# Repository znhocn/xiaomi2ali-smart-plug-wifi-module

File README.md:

# Xiaomi2Ali Smart Plug WiFi Module

Xiaomi Smart Plug WiFi Module to Ali 86 Smart Plug Adapter board

此项目是把从[米家智能插座基础版](https://www.mi.com/mj-socket/)里拆卸下来的 WiFi 模块转换成可供阿里智能插座-86型墙壁插座使用的模块。

使用小米的 WiFi 模块替换原有阿里智能的 WiFi 模块，实现使用米家APP控制插座，并且支持小爱同学控制。

目前米家生态链里没有直接使用 WiFi 的86型墙壁智能插座。

支持阿里86型墙壁插座的 10A 与 16A 的 WiFi 模块兼容性。

发给 PCB 厂家生产时建议使用 [Rev.B](Gerber/Rev.B) 版本。

某些厂家可能不支持半孔覆铜工艺，可用 Rev.B 版本发给厂家去生产。

使用 Rev.B 生产的 PCB 需要自己在通孔焊盘上划一刀再掰开，有必要还可以用锉刀再打磨一下断裂处。

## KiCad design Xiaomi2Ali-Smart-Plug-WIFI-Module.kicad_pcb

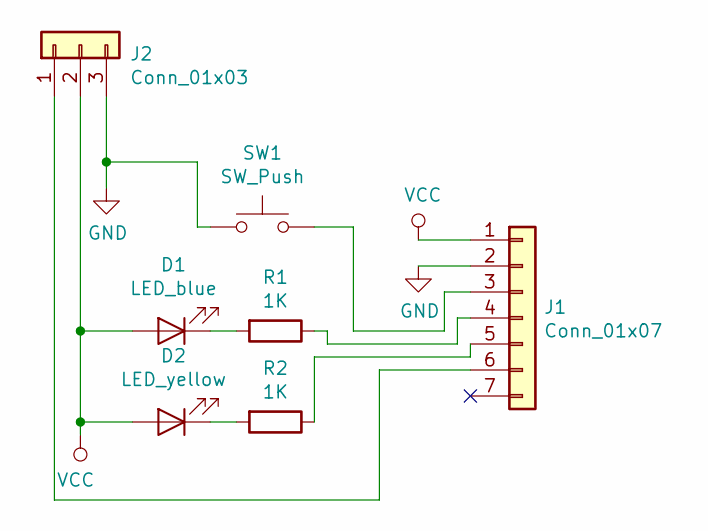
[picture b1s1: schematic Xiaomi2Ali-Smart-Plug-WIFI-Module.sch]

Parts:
D1: LED_blue; LED_1206_3216Metric
D2: LED_yellow; LED_1206_3216Metric
J1: Conn_01x07; PinHeader_1x07_P2.00mm_Vertical
J2: Conn_01x03; PinHeader_1x03_P2.54mm_Vertical
R1, R2: 1K; R_1206_3216Metric
SW1: SW_Push; SW_SPST_B3S-1000

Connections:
GND: J1.2, J2.3, SW1.1
unnamed: D1.1 (K), R1.2
unnamed: D2.1 (K), R2.2
unnamed: J1.3, SW1.2
unnamed: J1.4, R1.1
unnamed: J1.5, R2.1
unnamed: J1.6, J2.1
VCC: D1.2 (A), D2.2 (A), J1.1, J2.2

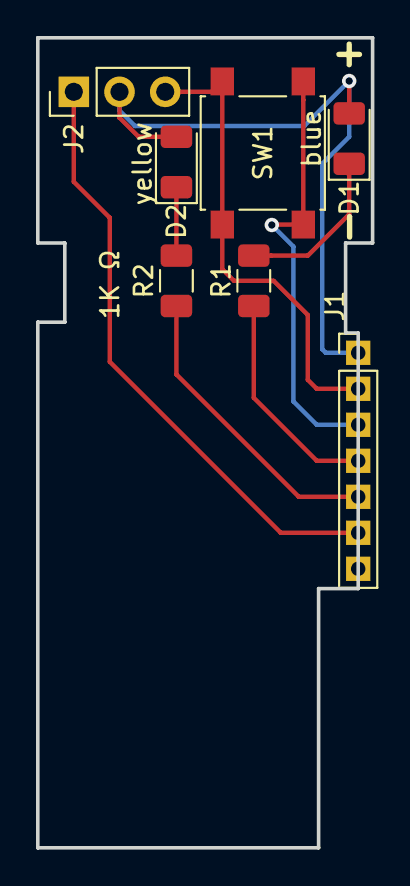
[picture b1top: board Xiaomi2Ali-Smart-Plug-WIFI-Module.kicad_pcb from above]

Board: 2 copper layers, 18.6 x 45.0 mm, 7 parts (0 on the bottom side), 8 nets.

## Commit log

2019-02-16 add .gitignore
2019-02-17 Updated: 2019-02-17 20:07:23
2019-02-17 Updated: 2019-02-17 20:11:17
2019-02-17 Updated: 2019-02-17 20:18:05
2019-02-17 Updated: 2019-02-18 00:24:23
2019-02-17 Updated: 2019-02-18 00:29:00
2019-02-17 Updated: 2019-02-18 00:42:54
2019-02-17 Updated: 2019-02-18 00:44:06
2019-02-18 Updated: 2019-02-18 13:14:53
2019-02-18 Updated: 2019-02-18 18:36:52
2019-02-19 Updated: 2019-02-20 00:25:07
2019-02-19 Updated: 2019-02-20 00:27:32
2019-02-20 Updated: 2019-02-20 16:21:37
2019-02-22 Updated: 2019-02-22 14:43:09
2019-02-22 Updated: 2019-02-22 15:01:56
2019-02-22 Updated: 2019-02-22 15:04:32
2019-02-22 Updated: 2019-02-22 15:56:17
2019-02-22 Updated: 2019-02-22 16:02:09
2019-02-22 Updated: 2019-02-22 16:02:28
2019-02-23 Updated: 2019-02-23 13:26:42
2019-02-23 Updated: 2019-02-23 13:48:15
2019-02-23 Updated: 2019-02-23 16:31:06
